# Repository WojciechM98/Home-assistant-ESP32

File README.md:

# Home-assistant-ESP32
Home assistand board using ESP32 controlled with MQTT protocol.

## Main purpose of Home assistant board
The project was created with the thought of controlling LED strips with MQTT protocol via phone app. A moment later, the idea of controlling and connecting many devices appeared such as water pump for watering plants plants, temperature sensors, lamps and so on.

Prototype mainboard version 0.1 consist of:
- Espressif ESP32 S2 mini 1 chip,
- CP2102N series USB to UART bridge controller,
- XT30PW-M connector for powering board with up to 15V DC external power source,
- Onboard 3.3V and 5V buck converters capable of 3A current load each,
- 4 I/O molex KK254 4 pin connectors,
- 8 output molex KK254 2 pin connectors,
- 2 connectors for additional expansion of the mainboard,
- UART pin header for externel programmer connection.

### I/O connectors
Each connector consists of ground and voltage pins (jumper selection 3.3V or 5V), output signal and input signal with ESD protection schottky diodes.

### Output connectors
Output connector consists of voltage pin (jumper selection 3.3V, 5V or external power from XT30PW-M connector) and n-mosfet switching to ground. Those headers are capable of PWM control. Used DMN3023L mosfets are capable of 30V and up to 6.3A continous drain current. There is also super fast recovery DFLU1200-7 diode protecting device from reverse current flow.

### Additional expansion connectors
Those connectors uses the rest of gpio ESP pins and also provide SPI and I2C protocols.

## ACControl board
This board allows to control AC powered devices.
Control signals are seperated from AC side with SFH6156-1T optotransistors for safety purpose. AZ921-1A-12DE relays are used for switching AC current.

## TempSensRTC
Addidtional board for temperature measurement. Can be used with MAX31865 chip for resisatance temperature detectors (RTDs) or with MAX31855 chip that allows to use theremocouples like K-type thermocouple.

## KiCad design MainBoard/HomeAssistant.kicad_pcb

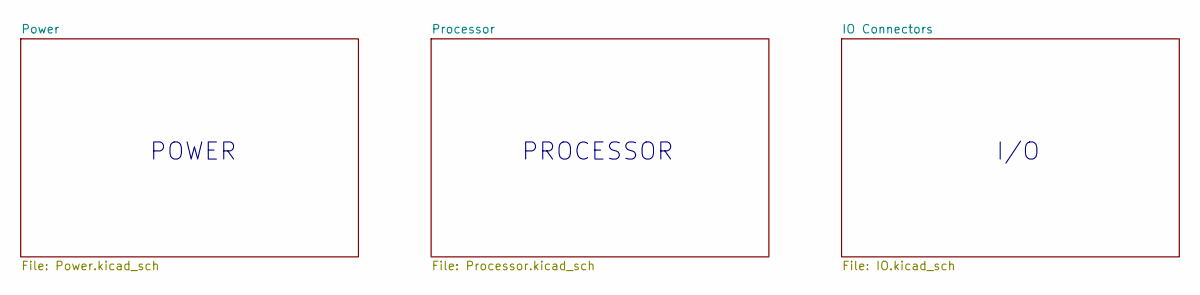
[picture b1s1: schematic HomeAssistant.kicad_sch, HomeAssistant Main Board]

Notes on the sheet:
I/O
POWER
PROCESSOR

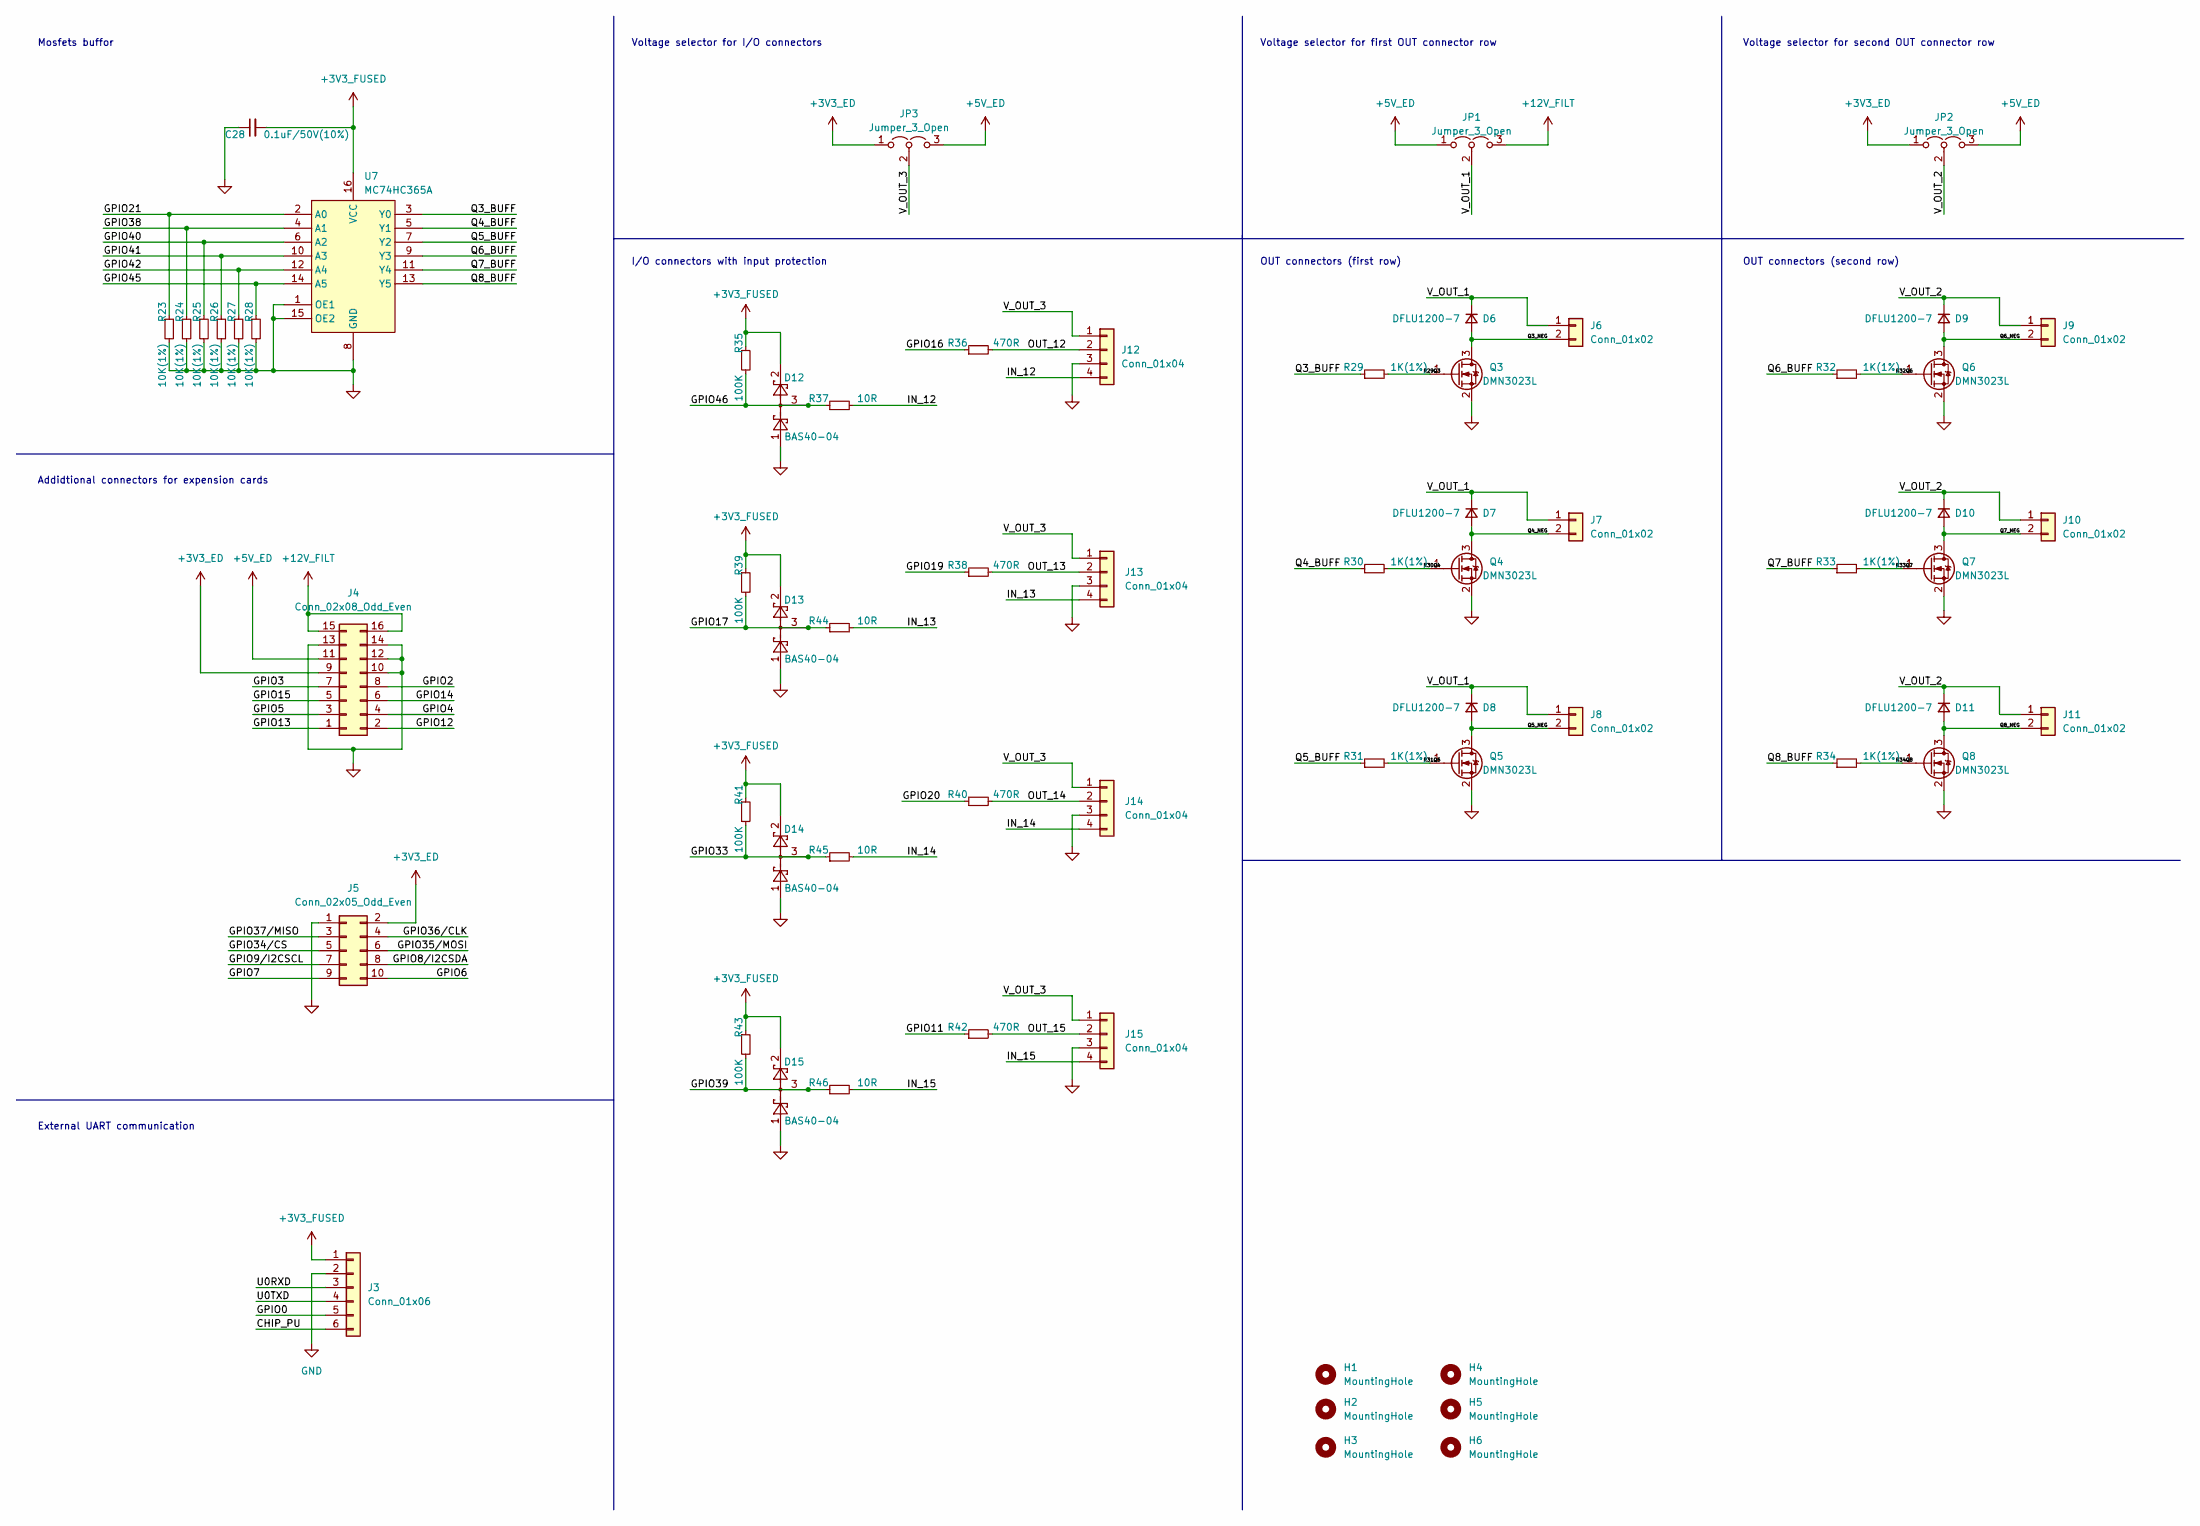
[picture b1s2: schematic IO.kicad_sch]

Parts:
C28: 0.1uF/50V(10%); C_0805_2012Metric
D6, D7, D8, D9, D10, D11: DFLU1200-7; DIODE_DFLU1200_1P93X3_DIO
D12, D13, D14, D15: BAS40-04; SOT-23
H1, H2, H3, H4: MountingHole; MountingHole_3.2mm_M3
H5, H6: MountingHole; SMTSO-M25-2ET
J3: Conn_01x06; PinSocket_1x06_P2.54mm_Vertical
J4: Conn_02x08_Odd_Even; PinSocket_2x08_P2.54mm_Vertical
J5: Conn_02x05_Odd_Even; PinSocket_2x05_P2.54mm_Vertical
J6, J7, J8, J9, J10, J11: Conn_01x02; Molex_KK-254_AE-6410-02A_1x02_P2.54mm_Vertical
J12, J13, J14, J15: Conn_01x04; Molex_KK-254_AE-6410-04A_1x04_P2.54mm_Vertical
JP1, JP2, JP3: Jumper_3_Open; PinHeader_1x03_P2.54mm_Vertical
Q3, Q4, Q5, Q6, Q7, Q8: DMN3023L; SOT-23
R23, R24, R25, R26, R27, R28: 10K(1%); R_0805_2012Metric
R29, R30, R31, R32, R33, R34: 1K(1%); R_0805_2012Metric
R35, R39, R41, R43: 100K; R_0805_2012Metric
R36, R38, R40, R42: 470R; R_0805_2012Metric
R37, R44, R45, R46: 10R; R_0805_2012Metric
U7: MC74HC365A; TSSOP-16_4.4x5mm_P0.65mm

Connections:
+3V3_ED: J4.9, J5.2, JP2.1 (A), JP3.1 (A); also elsewhere on the board
+3V3_FUSED: C28.2, D12.2, D13.2, D14.2, D15.2, J3.1, R35.1, R39.1, R41.1, R43.1, U7.16 (VCC); also elsewhere on the board
+5V_ED: J4.11, JP1.1 (A), JP2.3 (B), JP3.3 (B); also elsewhere on the board
+12V_FILT: J4.15, J4.16, JP1.3 (B); also elsewhere on the board
/IO Connectors/CHIP_PU: J3.6
/IO Connectors/GPIO0: J3.5
/IO Connectors/GPIO2: J4.8
/IO Connectors/GPIO3: J4.7
/IO Connectors/GPIO4: J4.4
/IO Connectors/GPIO5: J4.3
/IO Connectors/GPIO6: J5.10
/IO Connectors/GPIO7: J5.9
/IO Connectors/GPIO8/I2CSDA: J5.8
/IO Connectors/GPIO9/I2CSCL: J5.7
/IO Connectors/GPIO11: R42.1
/IO Connectors/GPIO12: J4.2
/IO Connectors/GPIO13: J4.1
/IO Connectors/GPIO14: J4.6
/IO Connectors/GPIO15: J4.5
/IO Connectors/GPIO17: D13.3, R39.2, R44.1
/IO Connectors/GPIO21: R23.1, U7.2 (A0)
/IO Connectors/GPIO33: D14.3, R41.2, R45.1
/IO Connectors/GPIO34/CS: J5.5
/IO Connectors/GPIO35/MOSI: J5.6
/IO Connectors/GPIO36/CLK: J5.4
/IO Connectors/GPIO37/MISO: J5.3
/IO Connectors/GPIO38: R24.1, U7.4 (A1)
/IO Connectors/GPIO39: D15.3, R43.2, R46.1
/IO Connectors/GPIO40: R25.1, U7.6 (A2)
/IO Connectors/GPIO41: R26.1, U7.10 (A3)
/IO Connectors/GPIO42: R27.1, U7.12 (A4)
/IO Connectors/GPIO45: R28.1, U7.14 (A5)
/IO Connectors/GPIO46: D12.3, R35.2, R37.1
/IO Connectors/IN_12: J12.4, R37.2
/IO Connectors/IN_13: J13.4, R44.2
/IO Connectors/IN_14: J14.4, R45.2
/IO Connectors/IN_15: J15.4, R46.2
/IO Connectors/OUT_12: J12.2, R36.2
/IO Connectors/OUT_13: J13.2, R38.2
/IO Connectors/OUT_14: J14.2, R40.2
/IO Connectors/OUT_15: J15.2, R42.2
/IO Connectors/Q3_BUFF: R29.1, U7.3 (Y0)
/IO Connectors/Q3_NEG: D6.2 (A), J6.2, Q3.3 (D)
/IO Connectors/Q4_BUFF: R30.1, U7.5 (Y1)
/IO Connectors/Q4_NEG: D7.2 (A), J7.2, Q4.3 (D)
/IO Connectors/Q5_BUFF: R31.1, U7.7 (Y2)
/IO Connectors/Q5_NEG: D8.2 (A), J8.2, Q5.3 (D)
/IO Connectors/Q6_BUFF: R32.1, U7.9 (Y3)
/IO Connectors/Q6_NEG: D9.2 (A), J9.2, Q6.3 (D)
/IO Connectors/Q7_BUFF: R33.1, U7.11 (Y4)
/IO Connectors/Q7_NEG: D10.2 (A), J10.2, Q7.3 (D)
/IO Connectors/Q8_BUFF: R34.1, U7.13 (Y5)
/IO Connectors/Q8_NEG: D11.2 (A), J11.2, Q8.3 (D)
/IO Connectors/R29Q3: Q3.1 (G), R29.2
/IO Connectors/R30Q4: Q4.1 (G), R30.2
/IO Connectors/R31Q5: Q5.1 (G), R31.2
/IO Connectors/R32Q6: Q6.1 (G), R32.2
/IO Connectors/R33Q7: Q7.1 (G), R33.2
/IO Connectors/R34Q8: Q8.1 (G), R34.2
/IO Connectors/U0RXD: J3.3
/IO Connectors/U0TXD: J3.4
/IO Connectors/V_OUT_1: D6.1 (K), D7.1 (K), D8.1 (K), J6.1, J7.1, J8.1, JP1.2 (C)
/IO Connectors/V_OUT_2: D9.1 (K), D10.1 (K), D11.1 (K), J9.1, J10.1, J11.1, JP2.2 (C)
/IO Connectors/V_OUT_3: J12.1, J13.1, J14.1, J15.1, JP3.2 (C)
/Processor/GPIO16: R36.1; also elsewhere on the board
/Processor/GPIO19: R38.1; also elsewhere on the board
/Processor/GPIO20: R40.1; also elsewhere on the board
GND: C28.1, D12.1, D13.1, D14.1, D15.1, J3.2, J4.10, J4.12, J4.13, J4.14, J5.1, J12.3, J13.3, J14.3, J15.3, Q3.2 (S), Q4.2 (S), Q5.2 (S), Q6.2 (S), Q7.2 (S), Q8.2 (S), R23.2, R24.2, R25.2, R26.2, R27.2, R28.2, U7.1 (OE1), U7.8 (GND), U7.15 (OE2); also elsewhere on the board

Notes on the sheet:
OUT connectors (second row)
Voltage selector for second OUT connector row
Mosfets buffor
I/O connectors with input protection
External UART communication
Voltage selector for I/O connectors
OUT connectors (first row)
Voltage selector for first OUT connector row
Addidtional connectors for expension cards

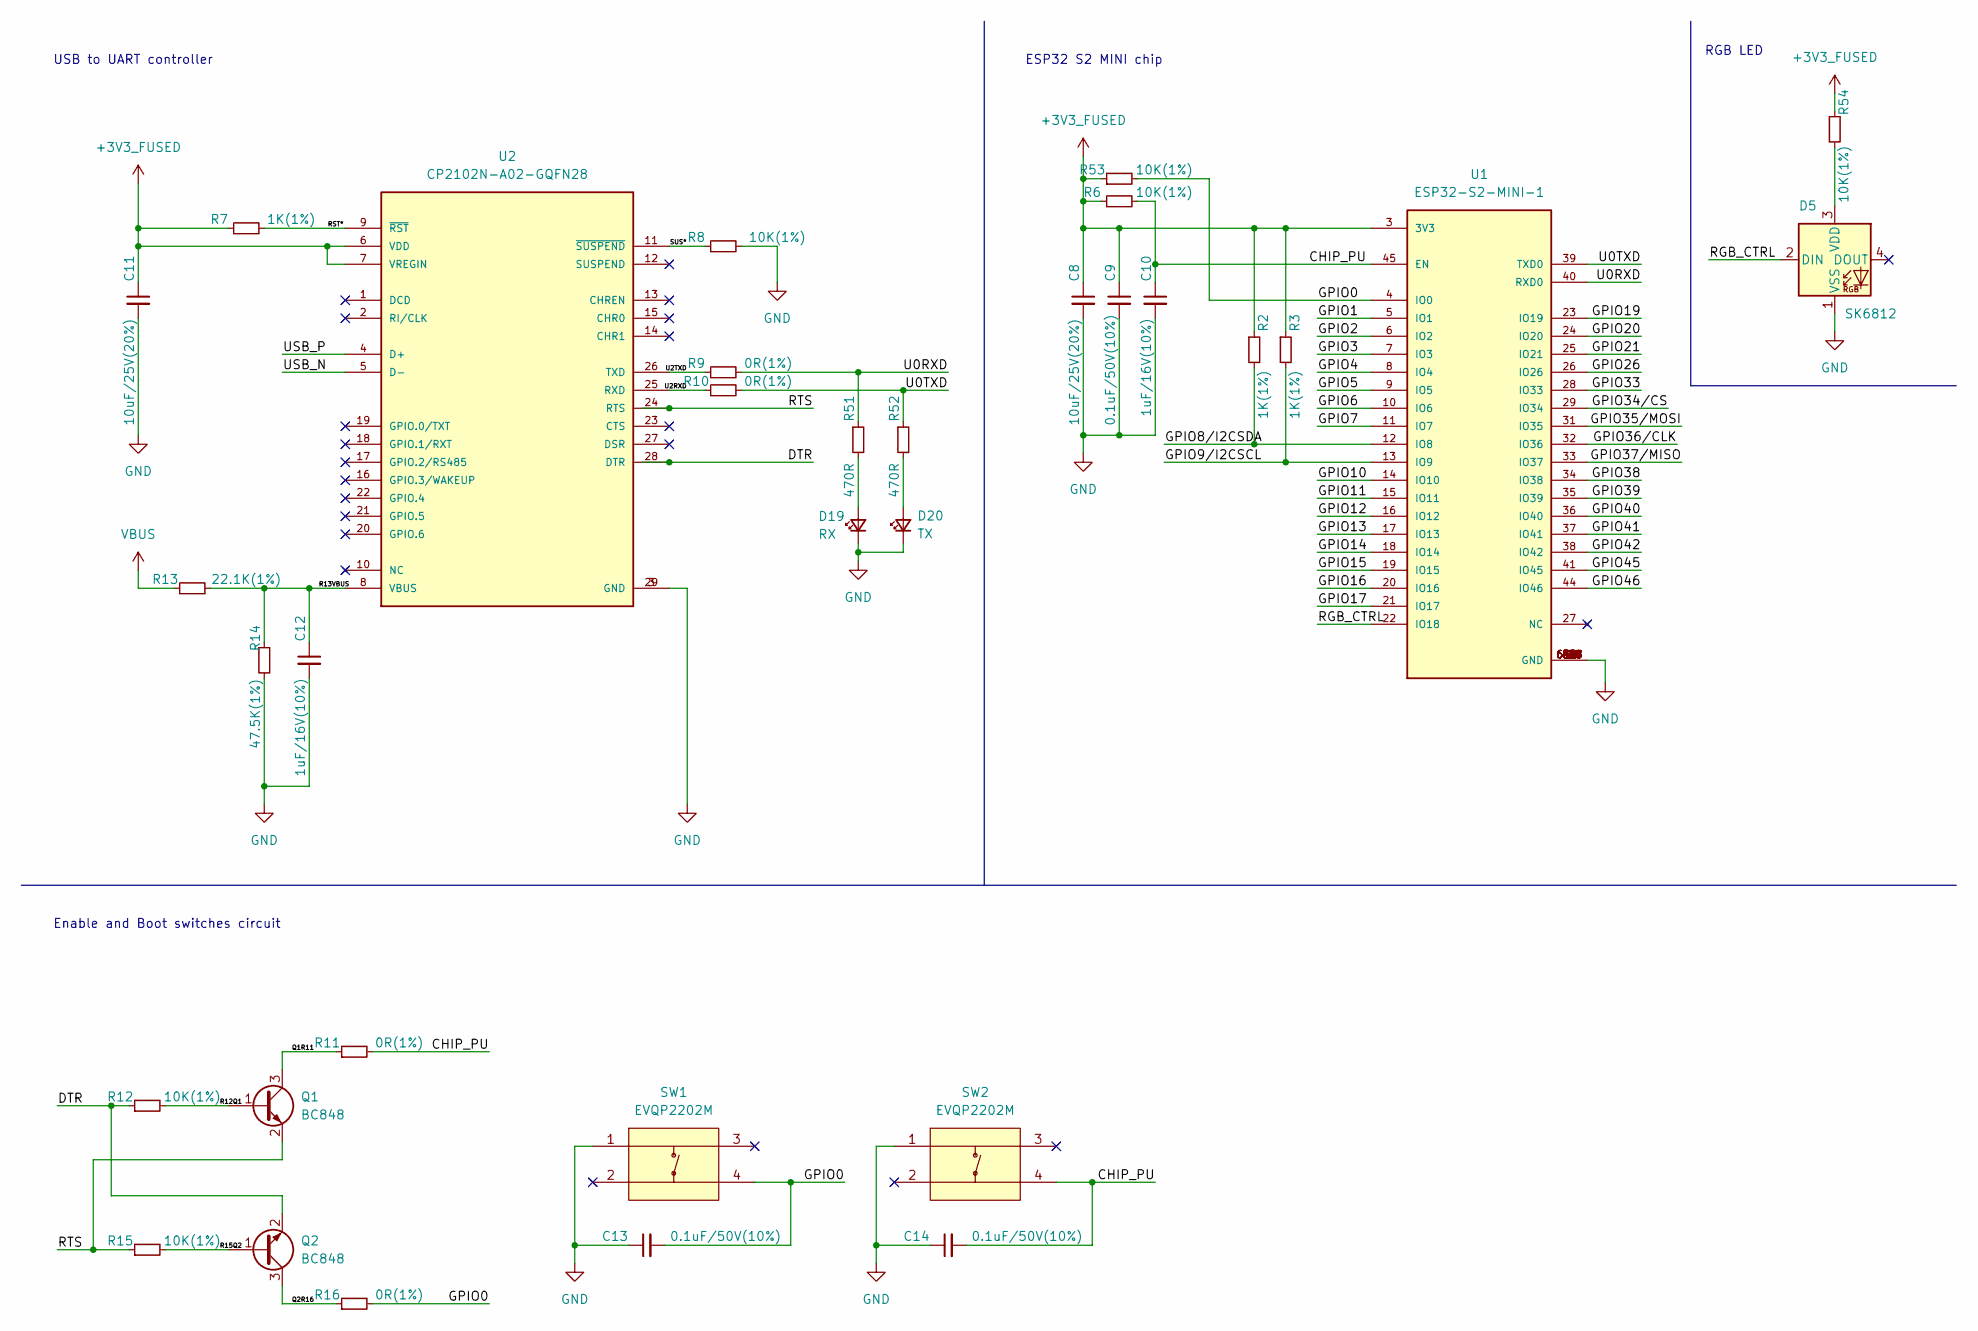
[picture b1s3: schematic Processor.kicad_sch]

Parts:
C8, C11: 10uF/25V(20%); C_0805_2012Metric
C9, C13, C14: 0.1uF/50V(10%); C_0805_2012Metric
C10, C12: 1uF/16V(10%); C_0805_2012Metric
D5: SK6812; LED_SK6812_PLCC4_5.0x5.0mm_P3.2mm
D19: RX; LED_0805_2012Metric
D20: TX; LED_0805_2012Metric
Q1, Q2: BC848; SOT-23
R2, R3, R7: 1K(1%); R_0805_2012Metric
R6, R8, R12, R15, R53, R54: 10K(1%); R_0805_2012Metric
R9, R10, R11, R16: 0R(1%); R_0805_2012Metric
R13: 22.1K(1%); R_0805_2012Metric
R14: 47.5K(1%); R_0805_2012Metric
R51, R52: 470R; R_0805_2012Metric
SW1, SW2: EVQP2202M; TACT_EVQP2202M
U1: ESP32-S2-MINI-1; XCVR_ESP32-S2-MINI-1; PARTREV 1.0
U2: CP2102N-A02-GQFN28; QFN50P500X500X80-29N; PARTREV 1.5

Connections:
+3V3_FUSED: C8.1, C9.1, C11.1, R2.1, R3.1, R6.1, R7.1, R53.1, R54.1, U1.3 (3V3), U2.6 (VDD), U2.7 (VREGIN); also elsewhere on the board
/Processor/CHIP_PU: C10.1, C14.2, R6.2, R11.2, SW2.4, U1.45 (EN)
/Processor/DTR: Q2.2 (E), R12.1, U2.28 (DTR)
/Processor/GPIO0: C13.2, R16.2, R53.2, SW1.4, U1.4 (IO0)
/Processor/GPIO1: U1.5 (IO1)
/Processor/GPIO2: U1.6 (IO2)
/Processor/GPIO3: U1.7 (IO3)
/Processor/GPIO4: U1.8 (IO4)
/Processor/GPIO5: U1.9 (IO5)
/Processor/GPIO6: U1.10 (IO6)
/Processor/GPIO7: U1.11 (IO7)
/Processor/GPIO8/I2CSDA: R2.2, U1.12 (IO8)
/Processor/GPIO9/I2CSCL: R3.2, U1.13 (IO9)
/Processor/GPIO10: U1.14 (IO10)
/Processor/GPIO11: U1.15 (IO11)
/Processor/GPIO12: U1.16 (IO12)
/Processor/GPIO13: U1.17 (IO13)
/Processor/GPIO14: U1.18 (IO14)
/Processor/GPIO15: U1.19 (IO15)
/Processor/GPIO16: U1.20 (IO16); also elsewhere on the board
/Processor/GPIO17: U1.21 (IO17)
/Processor/GPIO19: U1.23 (IO19); also elsewhere on the board
/Processor/GPIO20: U1.24 (IO20); also elsewhere on the board
/Processor/GPIO21: U1.25 (IO21)
/Processor/GPIO26: U1.26 (IO26)
/Processor/GPIO33: U1.28 (IO33)
/Processor/GPIO34/CS: U1.29 (IO34)
/Processor/GPIO35/MOSI: U1.31 (IO35)
/Processor/GPIO36/CLK: U1.32 (IO36)
/Processor/GPIO37/MISO: U1.33 (IO37)
/Processor/GPIO38: U1.34 (IO38)
/Processor/GPIO39: U1.35 (IO39)
/Processor/GPIO40: U1.36 (IO40)
/Processor/GPIO41: U1.37 (IO41)
/Processor/GPIO42: U1.38 (IO42)
/Processor/GPIO45: U1.41 (IO45)
/Processor/GPIO46: U1.44 (IO46)
/Processor/Q1R11: Q1.3 (C), R11.1
/Processor/Q2R16: Q2.3 (C), R16.1
/Processor/R12Q1: Q1.1 (B), R12.2
/Processor/R13VBUS: C12.1, R13.2, R14.1, U2.8 (VBUS)
/Processor/R15Q2: Q2.1 (B), R15.2
/Processor/RGB_CTRL: D5.2 (DIN), U1.22 (IO18)
/Processor/RST*: R7.2, U2.9 (~RST)
/Processor/RTS: Q1.2 (E), R15.1, U2.24 (RTS)
/Processor/SUS*: R8.1, U2.11 (~SUSPEND)
/Processor/U0RXD: R9.2, R51.1, U1.40 (RXD0)
/Processor/U0TXD: R10.2, R52.1, U1.39 (TXD0)
/Processor/U2RXD: R10.1, U2.25 (RXD)
/Processor/U2TXD: R9.1, U2.26 (TXD)
/Processor/USB_N: U2.5 (D-)
/Processor/USB_P: U2.4 (D+)
GND: C8.2, C9.2, C10.2, C11.2, C12.2, C13.1, C14.1, D5.1 (VSS), D19.1 (K), D20.1 (K), R8.2, R14.2, SW1.1, SW2.1, U1.1 (GND), U1.2 (GND), U1.30 (GND), U1.42 (GND), U1.43 (GND), U1.46 (GND), U1.47 (GND), U1.48 (GND), U1.49 (GND), U1.50 (GND), U1.51 (GND), U1.52 (GND), U1.53 (GND), U1.54 (GND), U1.55 (GND), U1.56 (GND), U1.57 (GND), U1.58 (GND), U1.59 (GND), U1.60 (GND), U1.61 (GND), U1.61_1 (GND), U1.61_2 (GND), U1.61_3 (GND), U1.61_4 (GND), U1.61_5 (GND), U1.61_6 (GND), U1.61_7 (GND), U1.61_8 (GND), U1.62 (GND), U1.63 (GND), U1.64 (GND), U1.65 (GND), U2.3 (GND), U2.29 (GND); also elsewhere on the board
unnamed: D5.3 (VDD), R54.2
unnamed: D19.2 (A), R51.2
unnamed: D20.2 (A), R52.2
VBUS: R13.1; also elsewhere on the board

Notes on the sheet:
Enable and Boot switches circuit
RGB LED
USB to UART controller
ESP32 S2 MINI chip

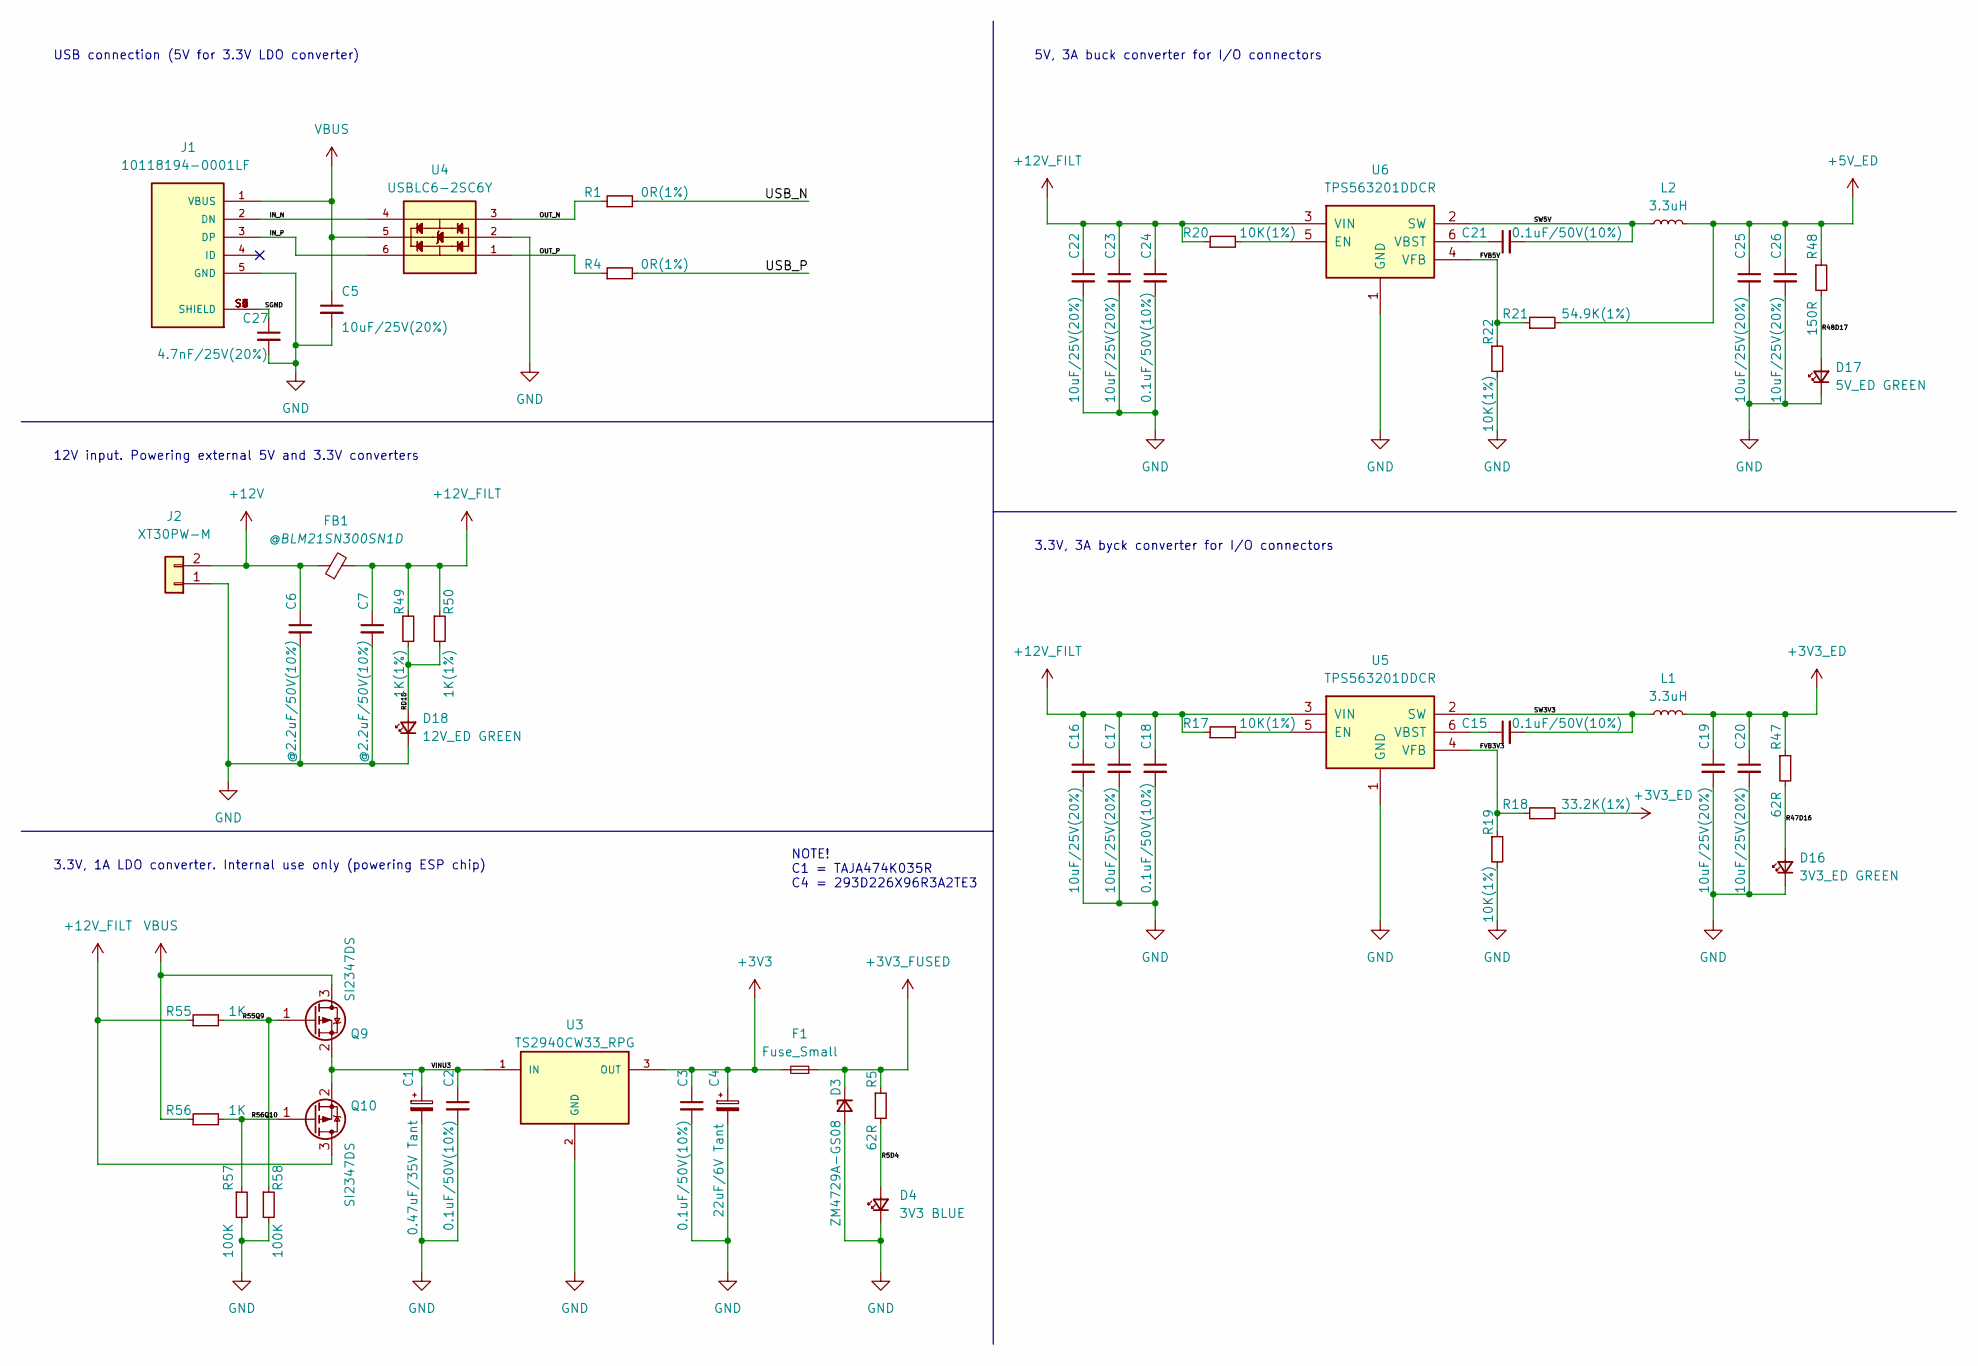
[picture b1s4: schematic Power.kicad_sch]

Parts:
C1: 0.47uF/35V Tant; CP_EIA-3216-18_Kemet-A
C2, C3, C15, C18, C21, C24: 0.1uF/50V(10%); C_0805_2012Metric
C4: 22uF/6V Tant; CP_EIA-3216-18_Kemet-A
C5, C16, C17, C19, C20, C22, C23, C25, C26: 10uF/25V(20%); C_0805_2012Metric
C6, C7: @2.2uF/50V(10%); C_0805_2012Metric
C27: 4.7nF/25V(20%); C_0805_2012Metric
D3: ZM4729A-GS08; D_MELF
D4: 3V3 BLUE; LED_0805_2012Metric
D16: 3V3_ED GREEN; LED_0805_2012Metric
D17: 5V_ED GREEN; LED_0805_2012Metric
D18: 12V_ED GREEN; LED_0805_2012Metric
F1: Fuse_Small; Fuse_0805_2012Metric
FB1: @BLM21SN300SN1D; Fuse_0805_2012Metric
J1: 10118194-0001LF; USB_AMPHENOL_10118194-0001LF; PARTREV D
J2: XT30PW-M; AMASS_XT30PW-M_1x02_P2.50mm_Horizontal
L1, L2: 3.3uH; INDM7676X355N
Q9, Q10: SI2347DS; TSOT-23
R1, R4: 0R(1%); R_0805_2012Metric
R5, R47: 62R; R_0805_2012Metric
R17, R19, R20, R22: 10K(1%); R_0805_2012Metric
R18: 33.2K(1%); R_0805_2012Metric
R21: 54.9K(1%); R_0805_2012Metric
R48: 150R; R_0805_2012Metric
R49, R50: 1K(1%); R_0805_2012Metric
R55, R56: 1K; R_0805_2012Metric
R57, R58: 100K; R_0805_2012Metric
U3: TS2940CW33_RPG; VREG_TS2940CW33_RPG; PARTREV E15
U4: USBLC6-2SC6Y; SOT95P280X145-6N
U5, U6: TPS563201DDCR; SOT95P280X110-6N; PARTREV December 2015

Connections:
+3V3: C3.1, C4.1, F1.2, U3.3 (OUT)
+3V3_ED: C19.1, C20.1, L1.2, R18.2, R47.1; also elsewhere on the board
+3V3_FUSED: D3.1 (K), F1.1, R5.1; also elsewhere on the board
+5V_ED: C25.1, C26.1, L2.2, R21.2, R48.1; also elsewhere on the board
+12V: C6.1, FB1.1, J2.2
+12V_FILT: C7.1, C16.1, C17.1, C18.1, C22.1, C23.1, C24.1, FB1.2, Q10.3 (D), R17.1, R20.1, R49.1, R50.1, R55.1, U5.3 (VIN), U6.3 (VIN); also elsewhere on the board
/Power/FVB3V3: R18.1, R19.1, U5.4 (VFB)
/Power/FVB5V: R21.1, R22.1, U6.4 (VFB)
/Power/IN_N: J1.2 (DN), U4.4
/Power/IN_P: J1.3 (DP), U4.6
/Power/OUT_N: R1.1, U4.3
/Power/OUT_P: R4.1, U4.1
/Power/R5D4: D4.2 (A), R5.2
/Power/R47D16: D16.2 (A), R47.2
/Power/R48D17: D17.2 (A), R48.2
/Power/R55Q9: Q9.1 (G), R55.2, R58.1
/Power/R56Q10: Q10.1 (G), R56.2, R57.1
/Power/RD18: D18.2 (A), R49.2, R50.2
/Power/SGND: C27.1, J1.S1 (SHIELD), J1.S2 (SHIELD), J1.S3 (SHIELD), J1.S4 (SHIELD), J1.S5 (SHIELD), J1.S6 (SHIELD)
/Power/SW3V3: C15.2, L1.1, U5.2 (SW)
/Power/SW5V: C21.2, L2.1, U6.2 (SW)
/Power/USB_N: R1.2
/Power/USB_P: R4.2
/Power/VINU3: C1.1, C2.1, Q9.2 (S), Q10.2 (S), U3.1 (IN)
GND: C1.2, C2.2, C3.2, C4.2, C5.2, C6.2, C7.2, C16.2, C17.2, C18.2, C19.2, C20.2, C22.2, C23.2, C24.2, C25.2, C26.2, C27.2, D3.2 (A), D4.1 (K), D16.1 (K), D17.1 (K), D18.1 (K), J1.5 (GND), J2.1, R19.2, R22.2, R57.2, R58.2, U3.2 (GND), U4.2, U5.1 (GND), U6.1 (GND); also elsewhere on the board
unnamed: C15.1, U5.6 (VBST)
unnamed: C21.1, U6.6 (VBST)
unnamed: R17.2, U5.5 (EN)
unnamed: R20.2, U6.5 (EN)
VBUS: C5.1, J1.1 (VBUS), Q9.3 (D), R56.1, U4.5; also elsewhere on the board

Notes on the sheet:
3.3V, 3A byck converter for I/O connectors
5V, 3A buck converter for I/O connectors
USB connection (5V for 3.3V LDO converter)
3.3V, 1A LDO converter. Internal use only (powering ESP chip)
NOTE! C1 = TAJA474K035R C4 = 293D226X96R3A2TE3
12V input. Powering external 5V and 3.3V converters
